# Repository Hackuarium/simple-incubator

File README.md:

# Simple incubator

The goal is to create a simple controller of temperature for an incubator.

## Pinout

| Pin Port | Function | Incubator Functions       | Description                                                                                              |
| -------- | -------- | ------------------------- | -------------------------------------------------------------------------------------------------------- |
| PC6      | /RESET   | /RESET                    | - Low level Reset pin. <br /> - DTS pin for Serial communication. <br /> - SS pin for SPI communication. |
| PD0      | 0        | RX                        | RX pin for Serial communication.                                                                         |
| PD1      | 1        | TX                        | TX pin for Serial communication.                                                                         |
| PD5      | 5        | OUT_FAN                   | Pin for fan control.                                                                                     |
| PD6      | 6        | PID_CONTROL               | Pin for PID control (need to have PWM).                                                                  |
| PB2      | 10       | OUT_ERROR                 | Pin for Error notification.                                                                              |
| PB3      | MOSI     | MOSI                      | MOSI pin for SPI communication.                                                                          |
| PB4      | MISO     | MISO                      | MISO pin for SPI communication.                                                                          |
| PB5      | 13       | SCK <br /> MONITORING_LED | - SCK pin for SPI communication. <br /> - Pin for Monitoring LED.                                        |
| PC0      | A0       | TEMP_EXT3                 | Pin for One-wire external temperature sensor 3.                                                          |
| PC1      | A1       | TEMP_EXT2                 | Pin for One-wire external temperature sensor 2.                                                          |
| PC2      | A2       | TEMP_EXT1                 | Pin for One-wire external temperature sensor 1.                                                          |
| PC3      | A3       | TEMP_PCB                  | Pin for One-wire temperature sensor in the PCB.                                                          |
| PC4      | SDA      | SDA                       | SDA pin for I2C communication (Slave I2C).                                                               |
| PC5      | SCL      | SCL                       | SCL pin for I2C communication (Slave I2C).                                                               |

## Power supply

- Plug for 12/18/24 V.
- LM7805 (DDPAK/TO-263 for 5 V @ 1.5 A) µC power supply.

## Schematic

- Minimal connections for ATMEGA328:

- Serial communication and programming with FTDI board:

- ISP communication for burn boatloader (and programming if you want it):

- Step-down converter to 5 V:

## Inspiration for PCB

- Resistor + Capacitor: 0805

* https://github.com/Hackuarium/esp-12e/tree/master/kica

  - ICSP - TAG connect - take care of pin mapping !
  - FTDI232.

## Get inspired from scale board

https://github.com/Hackuarium/beemos/tree/master/scale-i2c/eagle
https://github.com/Hackuarium/esp-12e/tree/master/kicad/libs

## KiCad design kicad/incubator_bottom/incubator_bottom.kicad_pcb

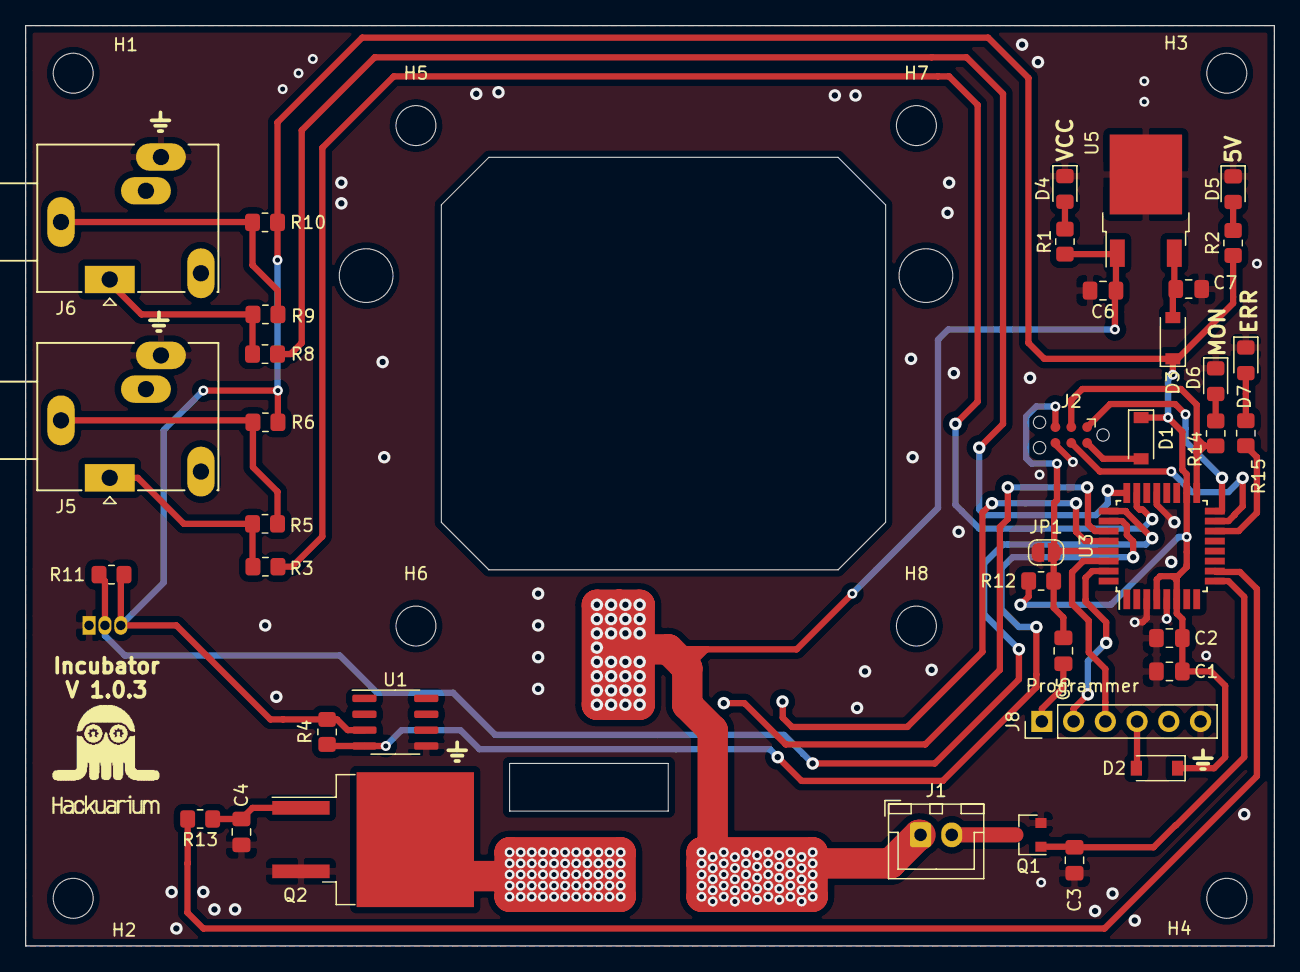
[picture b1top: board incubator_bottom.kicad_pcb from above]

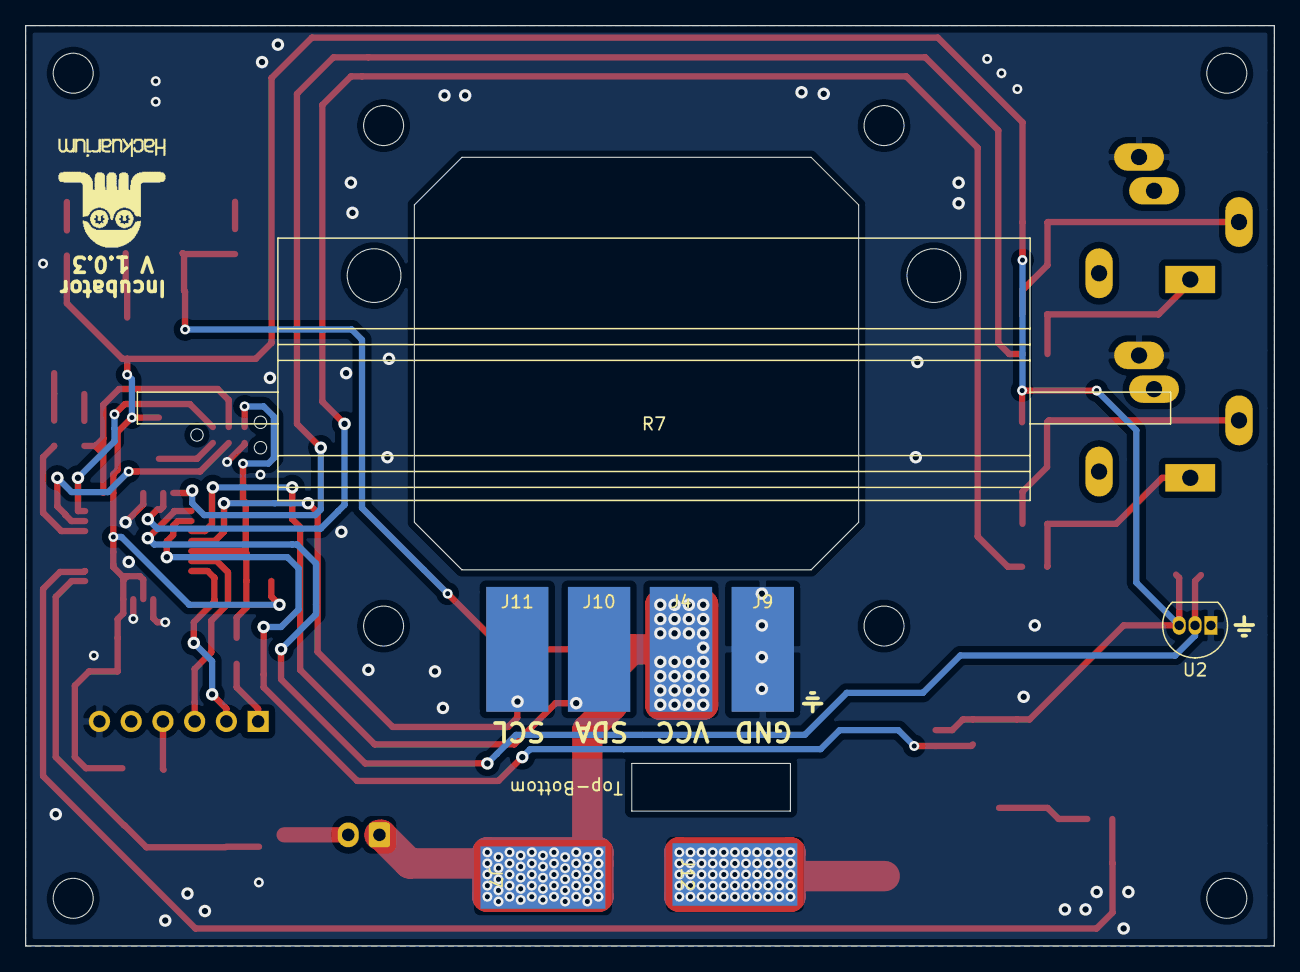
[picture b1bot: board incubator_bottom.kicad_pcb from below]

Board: 2 copper layers, 99.9 x 73.7 mm, 57 parts (9 on the bottom side), 33 nets.

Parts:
C1: 10u; C_0805_2012Metric_Pad1.18x1.45mm_HandSolder
C2, C3, C4, C5: 100n; C_0805_2012Metric_Pad1.18x1.45mm_HandSolder
C6: 0.33u; C_0805_2012Metric_Pad1.18x1.45mm_HandSolder
C7: 0.1u; C_0805_2012Metric_Pad1.18x1.45mm_HandSolder
D1, D2, D3: MBR0520LT; D_SOD-123
D4, D5, D6: GREEN; LED_0805_2012Metric_Pad1.15x1.40mm_HandSolder
D7: RED; LED_0805_2012Metric_Pad1.15x1.40mm_HandSolder
H1, H2, H3, H4, H5, H6, H7, H8: MountingHole; MountingHole_3.2mm_M3
J1: Conn_01x02; JST_XH_B2B-XH-A_1x02_P2.50mm_Vertical
J2: Conn_02x03_Odd_Even; Tag-Connect_TC2030-IDC-NL_2x03_P1.27mm_Vertical
J4, J7, J9, J10, J11, J12: Conn_01x01; SolderWirePad_1x01_SMD_5x10mm
J5, J6: AudioJack3_SwitchTR; Jack_3.5mm_Ledino_KB3SPRS_Horizontal
J8: Conn_01x06; PinHeader_1x06_P2.54mm_Vertical
JP1: SolderJumper_2_Open; SolderJumper-2_P1.3mm_Open_RoundedPad1.0x1.5mm
Q1: ZXMS6004; SOT-23
Q2: IPB80N03S4L-03; TO-263-2
R1, R14, R15: 10k; R_0805_2012Metric_Pad1.20x1.40mm_HandSolder
R2: 1k; R_0805_2012Metric_Pad1.20x1.40mm_HandSolder
R3, R8: 1K; R_0805_2012Metric_Pad1.20x1.40mm_HandSolder
R4, R5, R9, R11: 4.7k; R_0805_2012Metric_Pad1.20x1.40mm_HandSolder
R6, R10, R13: 100; R_0805_2012Metric_Pad1.20x1.40mm_HandSolder
R7: 100W4RJ
R12: 100k; R_0805_2012Metric_Pad1.20x1.40mm_HandSolder
U1: DS18B20Z; SOIC-8_3.9x4.9mm_P1.27mm
U2: DS18B20; TO-92_Inline
U3: ATmega328P-AU; TQFP-32_7x7mm_P0.8mm
U5: LM78M05_TO252; TO-252-2
logoHackuarium: logoHackuarium
logoHackuarium#2: logoHackuarium

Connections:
12V: C6.1, J1.1, J4.1, J7.1, R1.1, U5.1
ERROR: R15.2, U3.14
FAN: C3.1, Q1.1, U3.9
GND: C1.2, C2.2, C3.2, C4.2, C6.2, C7.2, D4.1, D5.1, D6.1, D7.1, J2.6, J5.R, J6.R, J8.6, J9.1, JP1.2, Q1.2, Q2.3, U1.5, U2.1, U3.3, U3.5, U3.21, U5.2
MISO: J2.1, U3.16
MOSI: J2.4, U3.15
unnamed: C4.1, Q2.1, R13.1
unnamed: C5.2, J8.1
unnamed: C7.1, D3.2, U5.3
unnamed: D1.2, J2.2
unnamed: D2.2, J8.4
unnamed: D4.2, R1.2
unnamed: D5.2, R2.2
unnamed: D6.2, R14.1
unnamed: D7.2, R15.1
unnamed: J1.2, Q1.3
unnamed: J5.S, R5.1, R6.2
unnamed: J5.T, R3.1, R5.2
unnamed: J6.S, R9.1, R10.2
unnamed: J6.T, R8.1, R9.2
unnamed: J12.1, Q2.2
ONE-WIRE-1: R4.2, U1.4, U3.26
ONE-WIRE-2: R11.2, U2.2, U3.25
ONE-WIRE-3: R8.2, U3.24
ONE-WIRE-4: R3.2, U3.23
PID: R13.2, U3.10
RX: J8.3, U3.30
SCK|MONITORING: J2.3, R14.2, U3.17
SCL: J11.1, U3.28
SDA: J10.1, U3.27
TX: J8.2, U3.31
VIN: C1.1, C2.1, D1.1, D2.1, D3.1, R2.1, R4.1, R6.1, R10.1, R11.1, R12.1, U1.3, U2.3, U3.4, U3.6, U3.18
~RESET: C5.1, J2.5, JP1.1, R12.2, U3.29

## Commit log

2019-03-12 rework fan and heating
2019-03-12 update schema
2019-03-12 update pcb
2019-03-19 update kicad
2019-04-16 The footprint should have changed to simple footprint design with 9 pads and a hole.
2019-05-07 last weeks updates
2021-08-03 chore: remove old design
2021-08-03 fix: add .gitignore
2021-08-06 build: Kicad PCB in proccess
2021-08-22 refactor: Kicad design updated
2021-08-23 feat: Platformio code
2021-08-23 feat: ibom generated
2021-08-23 fix: ibom link
2021-08-23 fix: ibom preview
2021-09-11 updated: previous travel
2021-09-13 updated: first push in Lau
2021-09-13 updated: first push in Lau-s
2021-09-13 updated: first push in Lau-ss
2021-09-13 updated: first push in Lauss
2021-09-13 updated: first push in Laussa
2021-09-14 fix: Power resistor size
2021-09-14 fix: Power resistor size and position
2021-09-15 fix: fan connection
2021-09-15 refactor:Step-down IC was changed
2021-09-15 refactor:rotated layer
2021-09-16 test: power resistor
2021-09-16 fix: Routes and positions for Power resistor, 5V Step-down and uC were changed
2021-09-20 refactor: Fan/resistor position, pad top-bottom
2021-09-20 refactor: Power supply
2021-09-20 refactor: Power supply pads
2021-09-21 refactor: final test version
2021-09-21 feat: gerber of version v1.0.0
2021-10-02 build: platformIO configuration and first code
2021-10-02 docs: config for USBTinyISP programmer
2021-10-03 fix: hack folder
2021-10-04 fix: Serial, EEPROM and Monitoring work
2021-10-06 fix: Code for simple-incubator in PlatformIO is ok
2021-10-07 feat: Correct pin for incubator pins, create FLAG and ERROR for resistor temperature
2021-11-05 feat: upload by USBTinyISP and run fuses option
2021-11-05 refactor: check code
2021-11-05 perf: BioParams.h
2021-11-05 fix: BioStepsThread
2021-11-05 fix: BioFunc
2021-11-05 fix: Params
2021-11-05 fix: SerialSpecific
2021-11-05 fix: Status
2021-11-05 fix: program with FTDI option
2021-11-05 fix: program options in platformio.ini
2021-11-05 feat: LCD
2021-11-10 fix: Compatibility with simple-i2c-screen
2021-11-15 fix: PWM for PID
2021-11-15 fix: PID control for v1.0.0 of PCB
2021-11-15 build: operational code for v1.0.0 board
2021-11-15 feat: start code for v1.0.1 board
2021-11-15 feat: v1.0.1 of board
2021-11-15 fix: solve issue for holes diameter
2021-11-16 fix: change diameter of holes and put logo
2021-11-16 feat: Monitoring and Error Thread for PCB V1.0.1
2021-11-16 docs: Pin configuration for Incubator V1.0.1
2021-11-16 docs: Pin mapping and main README for V1.0.1
2021-11-17 feat: WireSlave communication success!
2021-11-18 fix: version 1.0.2 of the PCB change size holes M4 -> M3 and changes their position
2021-11-18 refactor: version 1.0.3 of PCB for compatibility with simple-screen version
2021-11-18 refactor: clean BioParams.h
2021-11-18 test: I2C read and write parameters from LCD-push button from simple-i2c-screen
2021-11-19 refactor: delete unused constant
2021-11-19 feat: check printStack and reduce it
2022-02-12 refactor: Params.* -> Funcs.*
2022-02-12 refactor: BioParams.* to Params.*
2022-02-12 refactor: removed Bio tag from BioErrorThread.* and BioOneWireThread.*
2022-02-12 refactor: BioFanThread.* and BioPIDThread.* _ FanThread.* and PIDThread.*
2022-02-12 refactor: BioSerialThread.* -> SerialThread.*
2022-02-12 refactor: BioI2C.* and BioI2CThread.* -> I2C-.* and I2CThread.*
2022-02-12 fix: BioSem.* -> Sem.* and removed BioFunc.*
2022-02-12 refactor: BioHack.h removed
